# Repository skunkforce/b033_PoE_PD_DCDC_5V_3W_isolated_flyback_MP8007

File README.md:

# edgy_board number b033
This design is part of the [edgy board project](https://github.com/skunkforce/edgy_boards).

# getting started
This repository uses submodules. After cloning use the command 

```$ git submodule update --init --recursive```

to pull the submodules before opening the project with kicad. 

# Tests
Tests can be found in [TESTS.md](TESTS.md)

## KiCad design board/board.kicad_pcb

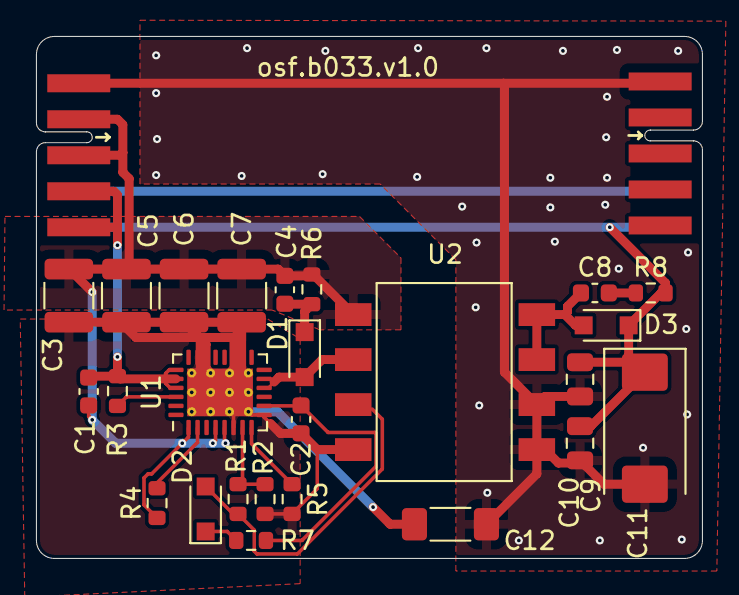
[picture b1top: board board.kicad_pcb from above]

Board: 2 copper layers, 37.0 x 29.0 mm, 27 parts (0 on the bottom side), 17 nets.

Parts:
C1, C2: 100n; C_0603_1608Metric
C3, C5, C6, C7: 2.2uF; C_1210_3225Metric
C4: 10nF; C_0603_1608Metric
C8: 10n; C_0603_1608Metric
C9, C10: 22uF; C_0805_2012Metric
C11: 220u; CP_EIA-7343-31_Kemet-D
C12: 1nF; C_1806_4516Metric
D1: BAV21WS-HE3-18; D_SOD-323_HandSoldering
D2: 1N4148; D_SOD-323_HandSoldering
D3: CUS15S30,H3F; D_SOD-323_HandSoldering
J1: 013_PoE_rectified; on_edge_2x05_device
J2: 003_power; on_edge_2x05_host
R1: 100k; R_0603_1608Metric
R2: 20k; R_0603_1608Metric
R3: 41.2R; R_0603_1608Metric
R4: 24.9k; R_0603_1608Metric
R5: 52.3k; R_0603_1608Metric
R6: 10k; R_0603_1608Metric
R7: 5k; R_0603_1608Metric
R8: 20R; R_0603_1608Metric
U1: MP8007; QFN-28-1EP_4x5mm_P0.5mm_EP2.65x3.65mm_ThermalVias
U2: POE30P-50L; Transformer_Coilcraft_POE30P

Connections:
/Controller/5V: C9.1, C10.1, C11.1, D3.1 (K), J1.10 (5V), J2.10 (5V), R8.2
/Controller/GNDPWR: C2.2, C3.2, C5.2, C6.2, C7.2, C12.2, R2.1, R5.2, U1.6 (MODE), U1.9 (AGND), U1.16 (GND), U1.17, U1.20 (RTN), U1.21, U1.29 (GND), U2.1 (B-)
/Controller/PoE+: C1.1, C3.1, C4.2, C5.1, C6.1, C7.1, J1.2 (48V), J1.3 (48V), R4.1, R6.2, U1.1 (AUX), U1.4 (VDD), U1.5 (FB2), U2.4 (P-)
/Controller/PoE-: C1.2, J1.4 (PoE_GND), J1.5 (PoE_GND), R3.2, U1.23 (VSS), U1.24, U1.25 (FTY)
GND: C9.2, C10.2, C11.2, C12.1, J1.1 (GND), J2.1 (GND), U2.7 (S2-), U2.8 (S-)
unnamed: C2.1, R7.2, U1.10 (VCC)
unnamed: C4.1, D1.1 (K), R6.1
unnamed: C8.1, D3.2 (A), U2.5 (S2+), U2.6 (S+)
unnamed: C8.2, R8.1
unnamed: D1.2 (A), U1.12 (SW), U1.13, U2.3 (P+)
unnamed: D2.1 (K), R7.1
unnamed: D2.2 (A), R1.1, U2.2 (B+)
unnamed: J1.9 (3.3V), J2.9 (3.3V)
unnamed: R1.2, R2.2, U1.7 (FB1)
unnamed: R3.1, U1.26 (CLASS)
unnamed: R4.2, U1.2 (DET)
unnamed: R5.1, U1.8 (ILIM)

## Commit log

2023-04-19 initial
2023-05-29 updated current limmit resistor
